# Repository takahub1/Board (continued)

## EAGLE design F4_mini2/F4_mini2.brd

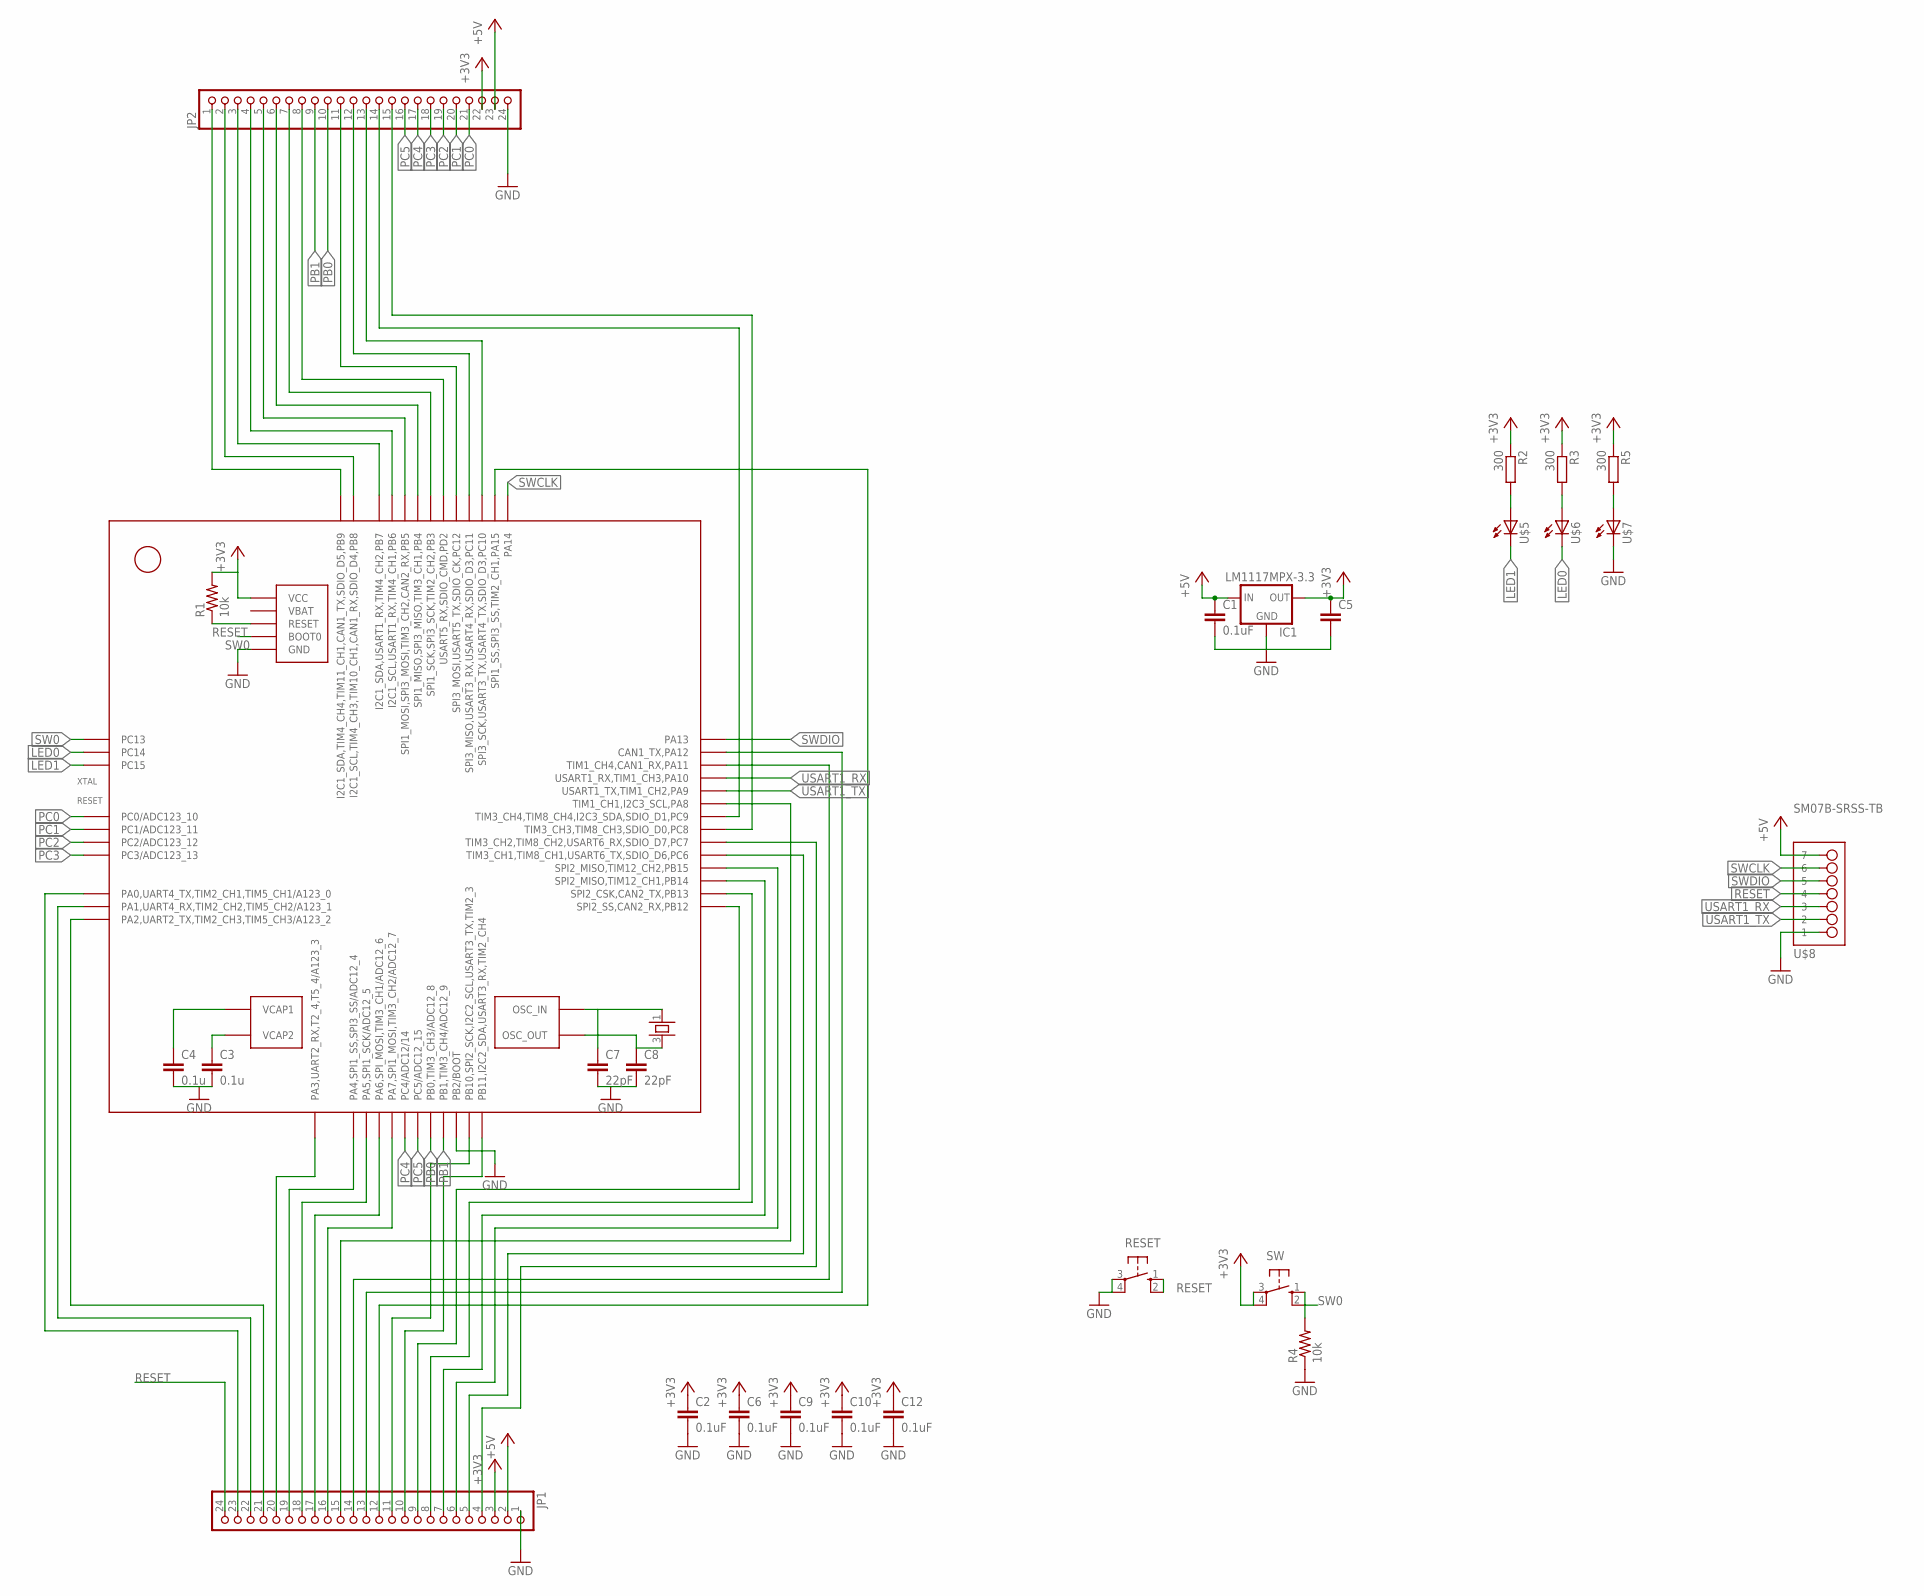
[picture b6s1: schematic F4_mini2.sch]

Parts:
C1: 0.1uF; C0603K
C2, C6, C9, C10, C12: 0.1uF; C0603
C3, C4: 0.1u; C0603K
C5: C-EUC0603K; C0603K
C7, C8: 22pF; C0603K
IC1: LM1117MPX-3.3; SOT223
JP1, JP2: PINHD-1X24; 1X24
R1, R4: 10k; R0603
R2, R3, R5: 300; R0603
RESET: 10-XX; B3F-10XX
SW: 10-XX; B3F-10XX
U$1: STM32F405_T; LQFP64
U$4: 25MHz; ASF
U$5, U$6, U$7: 0603
U$8: SM07B-SRSS-TB

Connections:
+3V3: C2.1, C5.1, C6.1, C9.1, C10.1, C12.1, IC1.2 (OUT1), IC1.4 (OUT), JP1.3, JP2.22, R1.2, R2.1, R3.1, R5.1, SW.3, SW.4 (P1), U$1.13 (VCC), U$1.19 (VCC), U$1.32 (VCC), U$1.48 (VCC), U$1.64 (VCC)
+5V: C1.1, IC1.3 (IN), JP1.2, JP2.23, U$8.P$7 (7)
A: JP2.3, U$1.59 (I2C1_SDA,USART1_RX,TIM4_CH2,PB7)
GND: C1.2, C2.2, C3.2, C4.2, C5.2, C6.2, C7.2, C8.2, C9.2, C10.2, C12.2, IC1.1 (GND), JP1.1, JP2.24, R4.1, RESET.3, RESET.4 (P1), U$1.12 (GND), U$1.18 (GND), U$1.28 (PB2/BOOT), U$1.63 (GND), U$7.C, U$8.P$1 (1)
LED0: U$1.3 (PC14), U$6.C
LED1: U$1.4 (PC15), U$5.C
unnamed: R2.2, U$5.A
unnamed: JP1.21, U$1.16 (PA2,UART2_TX,TIM2_CH3,TIM5_CH3/A123_2)
unnamed: JP1.23, U$1.14 (PA0,UART4_TX,TIM2_CH1,TIM5_CH1/A123_0)
unnamed: JP1.22, U$1.15 (PA1,UART4_RX,TIM2_CH2,TIM5_CH2/A123_1)
unnamed: JP1.15, U$1.41 (TIM1_CH1,I2C3_SCL,PA8)
unnamed: JP1.17, U$1.22 (PA6,SPI_MOSI,TIM3_CH1/ADC12_6)
unnamed: JP1.18, U$1.21 (PA5,SPI1_SCK/ADC12_5)
unnamed: JP1.19, U$1.20 (PA4,SPI1_SS,SPI3_SS/ADC12_4)
unnamed: JP1.20, U$1.17 (PA3,UART2_RX,T2_4,T5_4/A123_3)
unnamed: JP1.5, U$1.37 (TIM3_CH1,TIM8_CH1,USART6_TX,SDIO_D6,PC6)
unnamed: R3.2, U$6.A
unnamed: R5.2, U$7.A
unnamed: JP1.14, U$1.44 (TIM1_CH4,CAN1_RX,PA11)
unnamed: JP1.13, U$1.45 (CAN1_TX,PA12)
unnamed: JP1.4, U$1.38 (TIM3_CH2,TIM8_CH2,USART6_RX,SDIO_D7,PC7)
unnamed: JP1.16, U$1.23 (PA7,SPI1_MOSI,TIM3_CH2/ADC12_7)
unnamed: JP2.2, U$1.61 (I2C1_SCL,TIM4_CH3,TIM10_CH1,CAN1_RX,SDI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)
unnamed: JP2.1, U$1.62 (I2C1_SDA,TIM4_CH4,TIM11_CH1,CAN1_TX,SDI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)
unnamed: JP1.8, U$1.34 (SPI2_CSK,CAN2_TX,PB13)
unnamed: JP1.9, U$1.33 (SPI2_SS,CAN2_RX,PB12)
unnamed: JP1.10, U$1.30 (PB11,I2C2_SDA,USART3_RX,TIM2_CH4)
unnamed: JP1.11, U$1.29 (PB10,SPI2_SCK,I2C2_SCL,USART3_TX,TIM2_3)
unnamed: JP1.12, U$1.50 (SPI1_SS,SPI3_SS,TIM2_CH1,PA15)
unnamed: JP2.4, U$1.58 (I2C1_SCL,USART1_RX,TIM4_CH1,PB6)
unnamed: JP2.5, U$1.57 (SPI1_MOSI,SPI3_MOSI,TIM3_CH2,CAN2_RX,PB5)
unnamed: JP2.6, U$1.56 (SPI1_MISO,SPI3_MISO,TIM3_CH1,PB4)
unnamed: JP2.7, U$1.55 (SPI1_SCK,SPI3_SCK,TIM2_CH2,PB3)
unnamed: JP2.8, U$1.54 (USART5_RX,SDIO_CMD,PD2)
unnamed: JP2.11, U$1.53 (SPI3_MOSI,USART5_TX,SDIO_CK,PC12)
unnamed: JP2.12, U$1.52 (SPI3_MISO,USART3_RX,USART4_RX,SDIO_D3,P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)
unnamed: JP2.13, U$1.51 (SPI3_SCK,USART3_TX,USART4_TX,SDIO_D3,PC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)
unnamed: C3.1, U$1.47 (VCAP2)
unnamed: C4.1, U$1.31 (VCAP1)
unnamed: JP2.14, U$1.40 (TIM3_CH4,TIM8_CH4,I2C3_SDA,SDIO_D1,PC9)
unnamed: C7.1, U$1.5 (OSC_IN), U$4.1
unnamed: C8.1, U$1.6 (OSC_OUT), U$4.3
unnamed: JP2.15, U$1.39 (TIM3_CH3,TIM8_CH3,SDIO_D0,PC8)
PB0: JP2.10, U$1.26 (PB0,TIM3_CH3/ADC12_8)
PB1: JP2.9, U$1.27 (PB1,TIM3_CH4/ADC12_9)
PB14: JP1.7, U$1.35 (SPI2_MISO,TIM12_CH1,PB14)
PB15: JP1.6, U$1.36 (SPI2_MISO,TIM12_CH2,PB15)
PC0: JP2.21, U$1.8 (PC0/ADC123_10)
PC1: JP2.20, U$1.9 (PC1/ADC123_11)
PC2: JP2.19, U$1.10 (PC2/ADC123_12)
PC3: JP2.18, U$1.11 (PC3/ADC123_13)
PC4: JP2.17, U$1.24 (PC4/ADC12/14)
PC5: JP2.16, U$1.25 (PC5/ADC12_15)
RESET: JP1.24, R1.1, RESET.1 (S), RESET.2 (S1), U$1.7 (RESET), U$8.P$4 (4)
SW0: R4.2, SW.1 (S), SW.2 (S1), U$1.2 (PC13), U$1.60 (BOOT0)
SWCLK: U$1.49 (PA14), U$8.P$6 (6)
SWDIO: U$1.46 (PA13), U$8.P$5 (5)
USART1_RX: U$1.43 (USART1_RX,TIM1_CH3,PA10), U$8.P$3 (3)
USART1_TX: U$1.42 (USART1_TX,TIM1_CH2,PA9), U$8.P$2 (2)

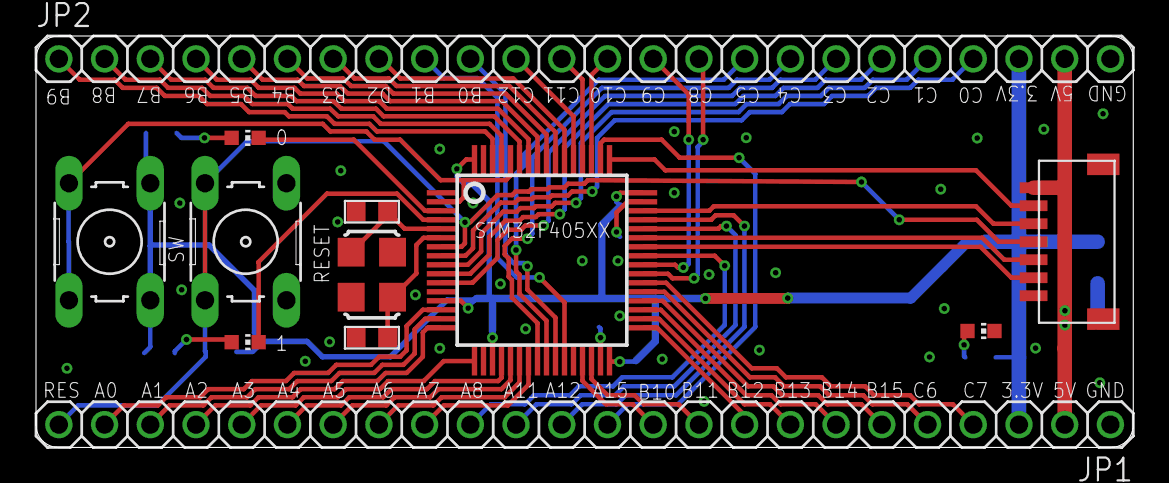
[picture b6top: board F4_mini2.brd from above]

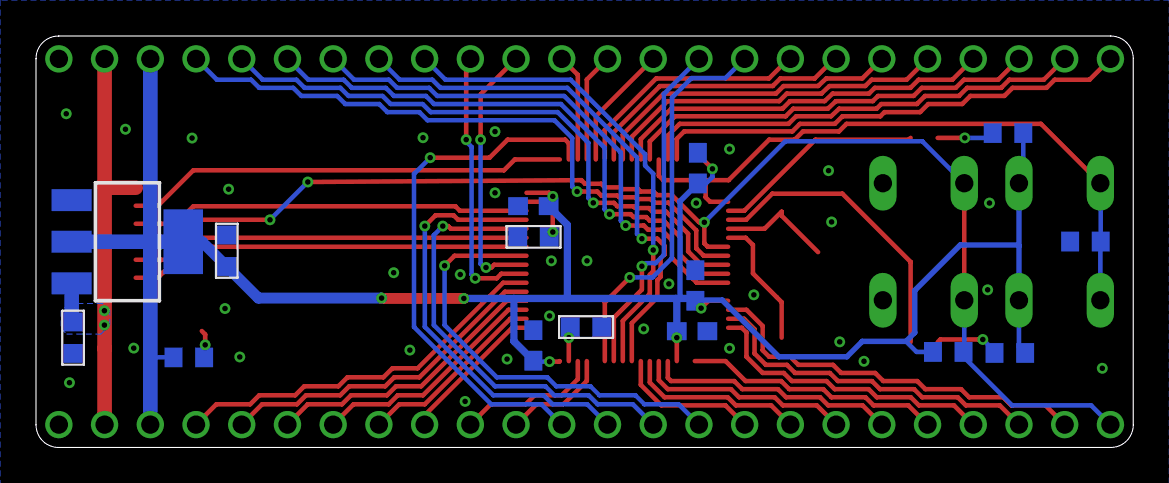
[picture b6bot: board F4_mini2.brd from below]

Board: 2 copper layers, 61.0 x 22.9 mm, 27 parts (15 on the bottom side), 59 nets.

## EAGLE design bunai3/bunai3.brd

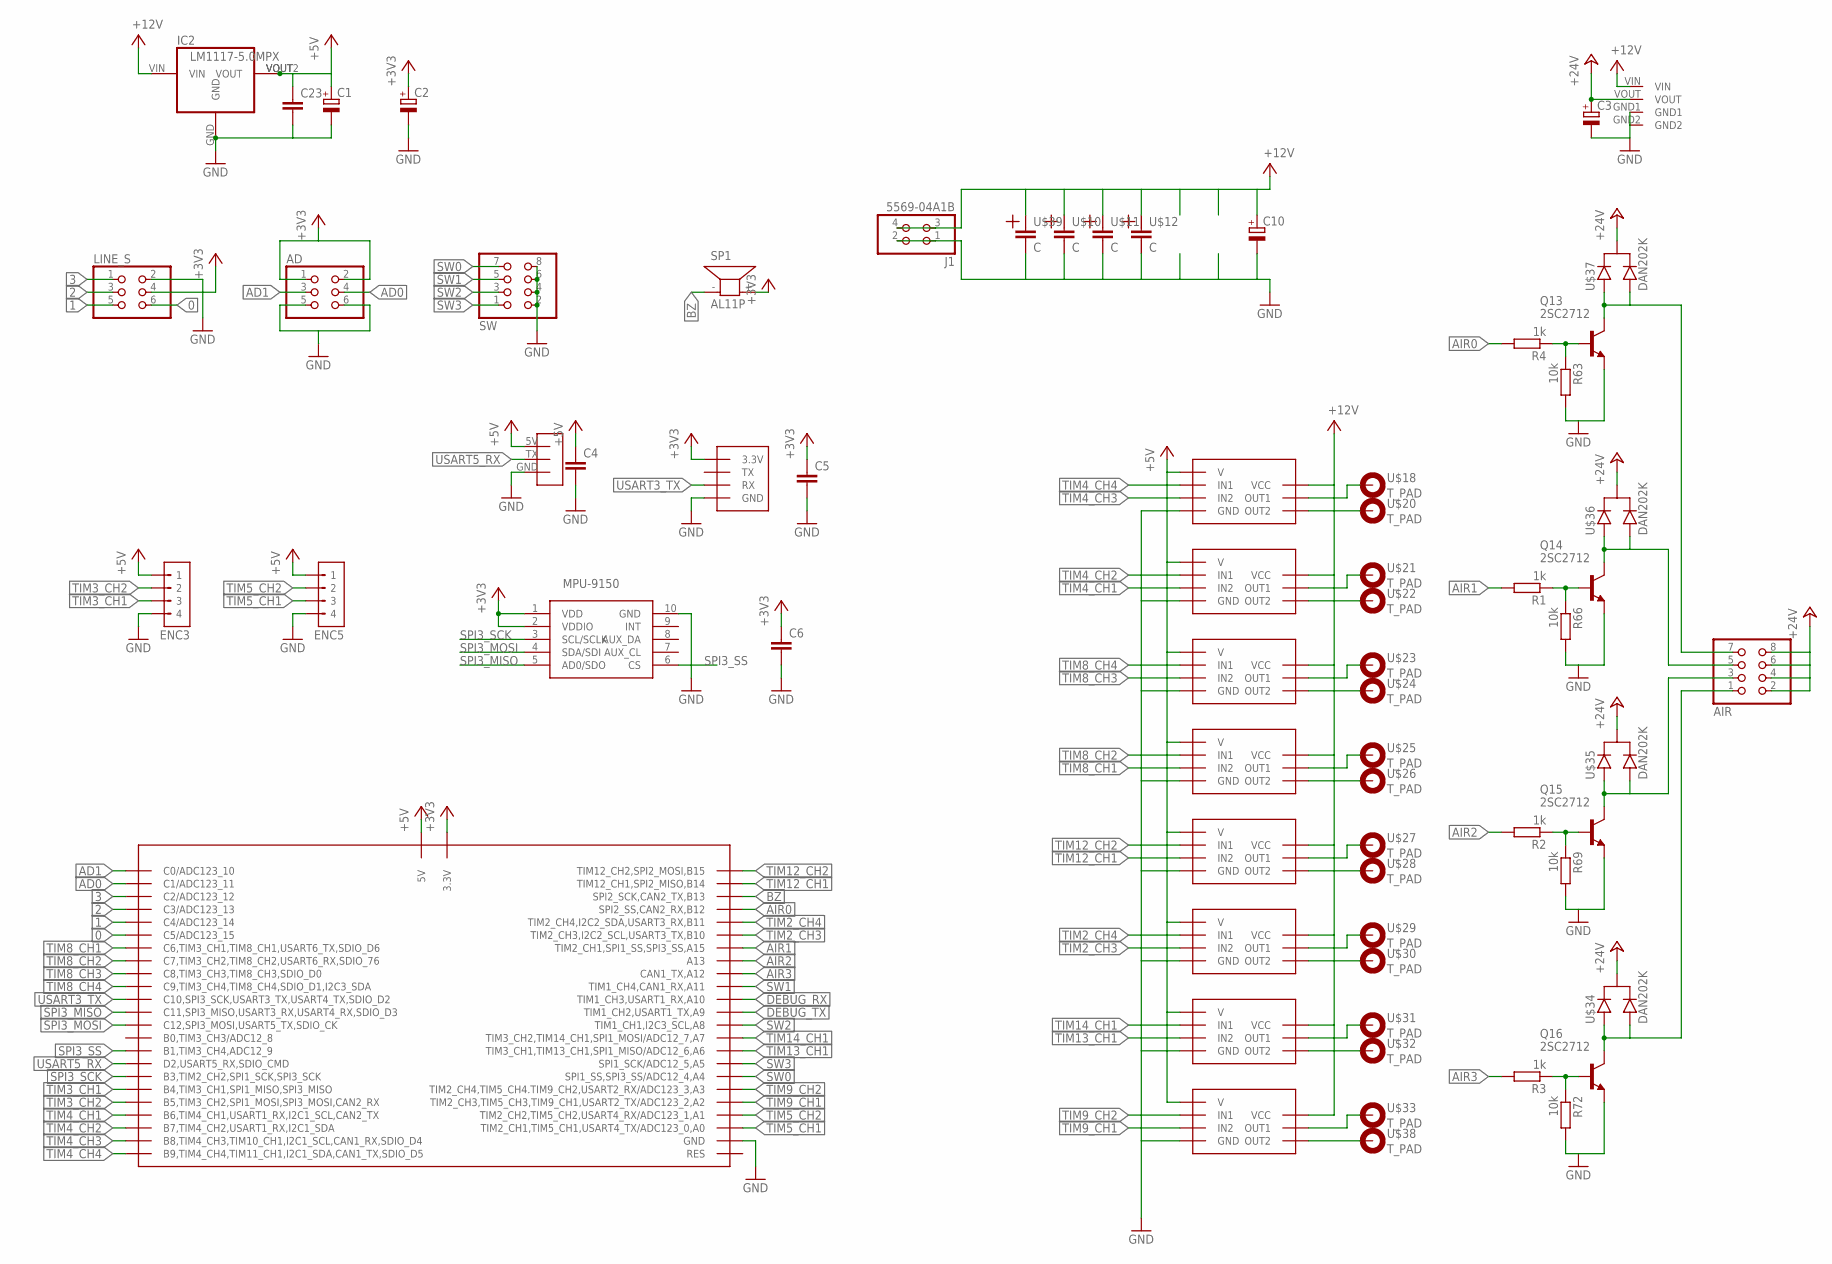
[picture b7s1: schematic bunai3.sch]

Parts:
AD: PINHD-2X3/90; 2X03/90
AIR: PINHD-2X4/90; 2X04/90
C1, C2, C3, C10: CPOL-EUE2.5-6; E2,5-6
C4, C5, C6: C-EU025-024X044; C025-024X044
C23: C-EUC0603K; C0603K
ENC3, ENC5: CN4-JST-XH-TOP; JST-B4B-XH-A
IC2: LM1117-5.0MPX; SOT223
J1: 5569-04A1B; 5569-04A1_2
LINE_S: PINHD-2X3/90; 2X03/90
MPU-9250: MPU-9250
Q13, Q14, Q15, Q16: 2SC2712; SC-59(TYPE1)
R1, R2, R3, R4: 1k; 0207/7
R63, R66, R69, R72: 10k; R0603
SP1: AL11P
SW: PINHD-2X4/90; 2X04/90
U$1: F4_T
U$2, U$3, U$4, U$5, U$6, U$7, U$8, U$9: BTM7752_T
U$10, U$11, U$12, U$39: C
U$16: LT3580
U$17: SBDBT_5V
U$18, U$20, U$21, U$22, U$23, U$24, U$25, U$26, U$27, U$28, U$29, U$30, U$31, U$32, U$33, U$38: T_PAD
U$19: XBEE_T
U$34, U$35, U$36, U$37: DAN202K; SC-59

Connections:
0: LINE_S.6, U$1.C5 (C5/ADC123_15)
1: LINE_S.5, U$1.C4 (C4/ADC123_14)
2: LINE_S.3, U$1.C3 (C3/ADC123_13)
3: LINE_S.1, U$1.C2 (C2/ADC123_12)
+3V3: AD.1, AD.2, C2.+, C5.1, C6.1, LINE_S.4, MPU-9250.1 (VDD), MPU-9250.2 (VDDIO), SP1.+ (2), U$1.3.3V, U$1.3.3V1 (3.3V), U$19.3.3V
+5V: C1.+, C4.1, C23.1, ENC3.1, ENC5.1, IC2.VOUT, IC2.VOUT2 (VOUT), U$1.5V, U$1.5V1 (5V), U$2.V, U$3.V, U$4.V, U$5.V, U$6.V, U$7.V, U$8.V, U$9.V, U$17.5V
+24V: AIR.2, AIR.4, AIR.6, AIR.8, C3.+, U$16.VOUT, U$34.K, U$35.K, U$36.K, U$37.K
AD0: AD.4, U$1.C1 (C1/ADC123_11)
AD1: AD.3, U$1.C0 (C0/ADC123_10)
AIR0: R4.2, U$1.B12 (SPI2_SS,CAN2_RX,B12)
AIR1: R1.2, U$1.A15 (TIM2_CH1,SPI1_SS,SPI3_SS,A15)
AIR2: R2.2, U$1.A13
AIR3: R3.2, U$1.A12 (CAN1_TX,A12)
BZ: SP1.- (1), U$1.B13 (SPI2_SCK,CAN2_TX,B13)
DEBUG_RX: U$1.A10 (TIM1_CH3,USART1_RX,A10)
DEBUG_TX: U$1.A9 (TIM1_CH2,USART1_TX,A9)
GND: AD.5, AD.6, C1.-, C2.-, C3.-, C4.2, C5.2, C6.2, C10.-, C23.2, ENC3.4, ENC5.4, IC2.GND, J1.1, J1.2, LINE_S.2, MPU-9250.10 (GND), Q13.E, Q14.E, Q15.E, Q16.E, R63.2, R66.2, R69.2, R72.2, SW.2, SW.4, SW.6, SW.8, U$1.GND1 (GND), U$1.GND2 (GND), U$1.GND3 (GND), U$2.GND1 (GND), U$2.GND2 (GND), U$2.GND3 (GND), U$3.GND1 (GND), U$3.GND2 (GND), U$3.GND3 (GND), U$4.GND1 (GND), U$4.GND2 (GND), U$4.GND3 (GND), U$5.GND1 (GND), U$5.GND2 (GND), U$5.GND3 (GND), U$6.GND1 (GND), U$6.GND2 (GND), U$6.GND3 (GND), U$7.GND1 (GND), U$7.GND2 (GND), U$7.GND3 (GND), U$8.GND1 (GND), U$8.GND2 (GND), U$8.GND3 (GND), U$9.GND1 (GND), U$9.GND2 (GND), U$9.GND3 (GND), U$16.GND1, U$16.GND2, U$17.GND, U$19.GND
unnamed: U$9.OUT11 (OUT1), U$9.OUT12 (OUT1), U$9.OUT13 (OUT1), U$9.OUT14 (OUT1), U$18.P$1
unnamed: U$9.OUT21 (OUT2), U$9.OUT22 (OUT2), U$9.OUT23 (OUT2), U$9.OUT24 (OUT2), U$20.P$1
unnamed: U$8.OUT11 (OUT1), U$8.OUT12 (OUT1), U$8.OUT13 (OUT1), U$8.OUT14 (OUT1), U$21.P$1
unnamed: U$8.OUT21 (OUT2), U$8.OUT22 (OUT2), U$8.OUT23 (OUT2), U$8.OUT24 (OUT2), U$22.P$1
unnamed: U$7.OUT11 (OUT1), U$7.OUT12 (OUT1), U$7.OUT13 (OUT1), U$7.OUT14 (OUT1), U$23.P$1
unnamed: U$7.OUT21 (OUT2), U$7.OUT22 (OUT2), U$7.OUT23 (OUT2), U$7.OUT24 (OUT2), U$24.P$1
unnamed: U$6.OUT11 (OUT1), U$6.OUT12 (OUT1), U$6.OUT13 (OUT1), U$6.OUT14 (OUT1), U$25.P$1
unnamed: U$6.OUT21 (OUT2), U$6.OUT22 (OUT2), U$6.OUT23 (OUT2), U$6.OUT24 (OUT2), U$26.P$1
unnamed: U$5.OUT11 (OUT1), U$5.OUT12 (OUT1), U$5.OUT13 (OUT1), U$5.OUT14 (OUT1), U$27.P$1
unnamed: U$5.OUT21 (OUT2), U$5.OUT22 (OUT2), U$5.OUT23 (OUT2), U$5.OUT24 (OUT2), U$28.P$1
unnamed: U$4.OUT11 (OUT1), U$4.OUT12 (OUT1), U$4.OUT13 (OUT1), U$4.OUT14 (OUT1), U$29.P$1
unnamed: U$4.OUT21 (OUT2), U$4.OUT22 (OUT2), U$4.OUT23 (OUT2), U$4.OUT24 (OUT2), U$30.P$1
unnamed: U$3.OUT11 (OUT1), U$3.OUT12 (OUT1), U$3.OUT13 (OUT1), U$3.OUT14 (OUT1), U$31.P$1
unnamed: U$3.OUT21 (OUT2), U$3.OUT22 (OUT2), U$3.OUT23 (OUT2), U$3.OUT24 (OUT2), U$32.P$1
unnamed: U$2.OUT11 (OUT1), U$2.OUT12 (OUT1), U$2.OUT13 (OUT1), U$2.OUT14 (OUT1), U$33.P$1
unnamed: U$2.OUT21 (OUT2), U$2.OUT22 (OUT2), U$2.OUT23 (OUT2), U$2.OUT24 (OUT2), U$38.P$1
unnamed: Q13.B, R4.1, R63.1
unnamed: AIR.7, Q13.C, U$37.A@1 (A1), U$37.A@2 (A2)
unnamed: Q14.B, R1.1, R66.1
unnamed: AIR.5, Q14.C, U$36.A@1 (A1), U$36.A@2 (A2)
unnamed: Q15.B, R2.1, R69.1
unnamed: AIR.3, Q15.C, U$35.A@1 (A1), U$35.A@2 (A2)
unnamed: AIR.1, Q16.C, U$34.A@1 (A1), U$34.A@2 (A2)
unnamed: Q16.B, R3.1, R72.1
SPI3_MISO: MPU-9250.5 (AD0/SDO), U$1.C11 (C11,SPI3_MISO,USART3_RX,USART4_RX,SDIO_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)
SPI3_MOSI: MPU-9250.4 (SDA/SDI), U$1.C12 (C12,SPI3_MOSI,USART5_TX,SDIO_CK)
SPI3_SCK: MPU-9250.3 (SCL/SCLK), U$1.B3 (B3,TIM2_CH2,SPI1_SCK,SPI3_SCK)
SPI3_SS: MPU-9250.6 (CS), U$1.B1 (B1,TIM3_CH4,ADC12_9)
SW0: SW.7, U$1.A4 (SPI1_SS,SPI3_SS/ADC12_4,A4)
SW1: SW.5, U$1.A11 (TIM1_CH4,CAN1_RX,A11)
SW2: SW.3, U$1.A8 (TIM1_CH1,I2C3_SCL,A8)
SW3: SW.1, U$1.A5 (SPI1_SCK/ADC12_5,A5)
TIM2_CH3: U$1.B10 (TIM2_CH3,I2C2_SCL,USART3_TX,B10), U$4.IN2
TIM2_CH4: U$1.B11 (TIM2_CH4,I2C2_SDA,USART3_RX,B11), U$4.IN1
TIM3_CH1: ENC3.3, U$1.B4 (B4,TIM3_CH1,SPI1_MISO,SPI3_MISO)
TIM3_CH2: ENC3.2, U$1.B5 (B5,TIM3_CH2,SPI1_MOSI,SPI3_MOSI,CAN2_RX)
TIM4_CH1: U$1.B6 (B6,TIM4_CH1,USART1_RX,I2C1_SCL,CAN2_TX), U$8.IN2
TIM4_CH2: U$1.B7 (B7,TIM4_CH2,USART1_RX,I2C1_SDA), U$8.IN1
TIM4_CH3: U$1.B8 (B8,TIM4_CH3,TIM10_CH1,I2C1_SCL,CAN1_RX,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), U$9.IN2
TIM4_CH4: U$1.B9 (B9,TIM4_CH4,TIM11_CH1,I2C1_SDA,CAN1_TX,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), U$9.IN1
TIM5_CH1: ENC5.3, U$1.A0 (TIM2_CH1,TIM5_CH1,USART4_TX/ADC123_0,A0)
TIM5_CH2: ENC5.2, U$1.A1 (TIM2_CH2,TIM5_CH2,USART4_RX/ADC123_1,A1)
TIM8_CH1: U$1.C6 (C6,TIM3_CH1,TIM8_CH1,USART6_TX,SDIO_D6), U$6.IN2
TIM8_CH2: U$1.C7 (C7,TIM3_CH2,TIM8_CH2,USART6_RX,SDIO_76), U$6.IN1
TIM8_CH3: U$1.C8 (C8,TIM3_CH3,TIM8_CH3,SDIO_D0), U$7.IN2
TIM8_CH4: U$1.C9 (C9,TIM3_CH4,TIM8_CH4,SDIO_D1,I2C3_SDA), U$7.IN1
TIM9_CH1: U$1.A2 (TIM2_CH3,TIM5_CH3,TIM9_CH1,USART2_TX/AD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), U$2.IN2
TIM9_CH2: U$1.A3 (TIM2_CH4,TIM5_CH4.TIM9_CH2,USART2_RX/AD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), U$2.IN1
TIM12_CH1: U$1.B14 (TIM12_CH1,SPI2_MISO,B14), U$5.IN2
TIM12_CH2: U$1.B15 (TIM12_CH2,SPI2_MOSI,B15), U$5.IN1
TIM13_CH1: U$1.A6 (TIM3_CH1,TIM13_CH1,SPI1_MISO/ADC12_6,A6), U$3.IN2
TIM14_CH1: U$1.A7 (TIM3_CH2,TIM14_CH1,SPI1_MOSI/ADC12_7,A7), U$3.IN1
USART3_TX: U$1.C10 (C10,SPI3_SCK,USART3_TX,USART4_TX,SDIO_D2), U$19.RX
USART5_RX: U$1.D2 (D2,USART5_RX,SDIO_CMD), U$17.TX (TX_5V)
V+: C10.+, IC2.VIN, J1.3, J1.4, U$2.VCC1 (VCC), U$2.VCC2 (VCC), U$2.VCC3 (VCC), U$2.VCC4 (VCC), U$3.VCC1 (VCC), U$3.VCC2 (VCC), U$3.VCC3 (VCC), U$3.VCC4 (VCC), U$4.VCC1 (VCC), U$4.VCC2 (VCC), U$4.VCC3 (VCC), U$4.VCC4 (VCC), U$5.VCC1 (VCC), U$5.VCC2 (VCC), U$5.VCC3 (VCC), U$5.VCC4 (VCC), U$6.VCC1 (VCC), U$6.VCC2 (VCC), U$6.VCC3 (VCC), U$6.VCC4 (VCC), U$7.VCC1 (VCC), U$7.VCC2 (VCC), U$7.VCC3 (VCC), U$7.VCC4 (VCC), U$8.VCC1 (VCC), U$8.VCC2 (VCC), U$8.VCC3 (VCC), U$8.VCC4 (VCC), U$9.VCC1 (VCC), U$9.VCC2 (VCC), U$9.VCC3 (VCC), U$9.VCC4 (VCC), U$16.VIN

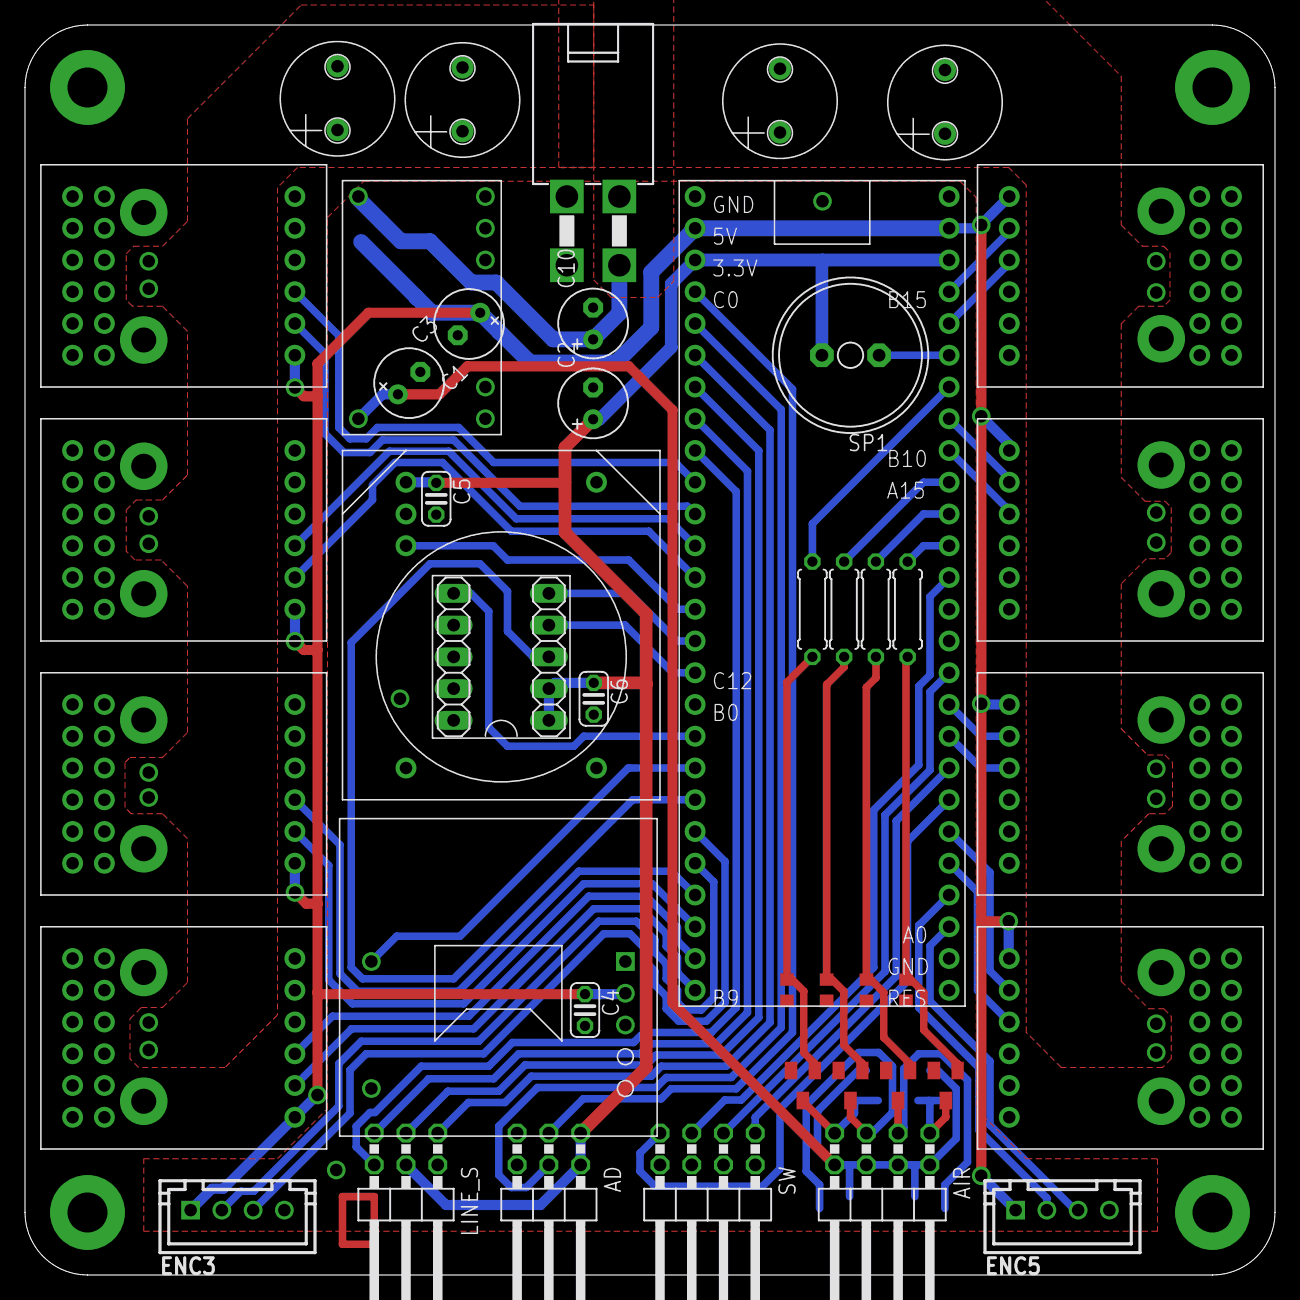
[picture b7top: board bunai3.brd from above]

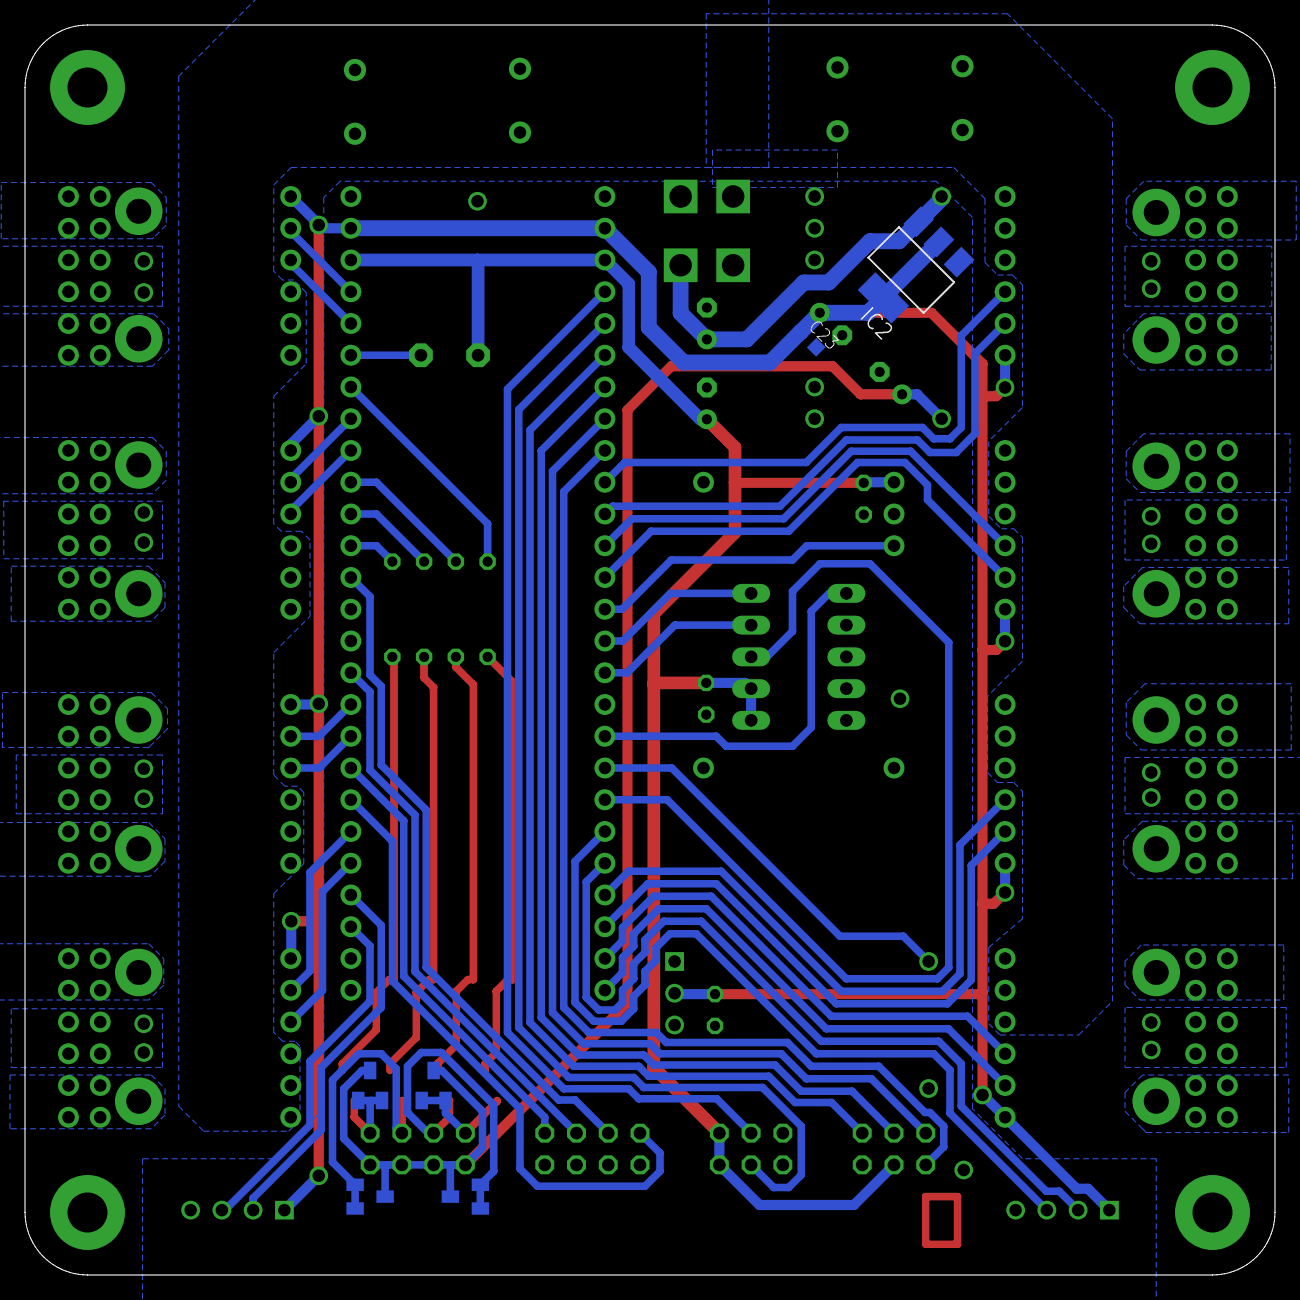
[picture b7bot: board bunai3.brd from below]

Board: 2 copper layers, 100.0 x 100.0 mm, 66 parts (6 on the bottom side), 70 nets.

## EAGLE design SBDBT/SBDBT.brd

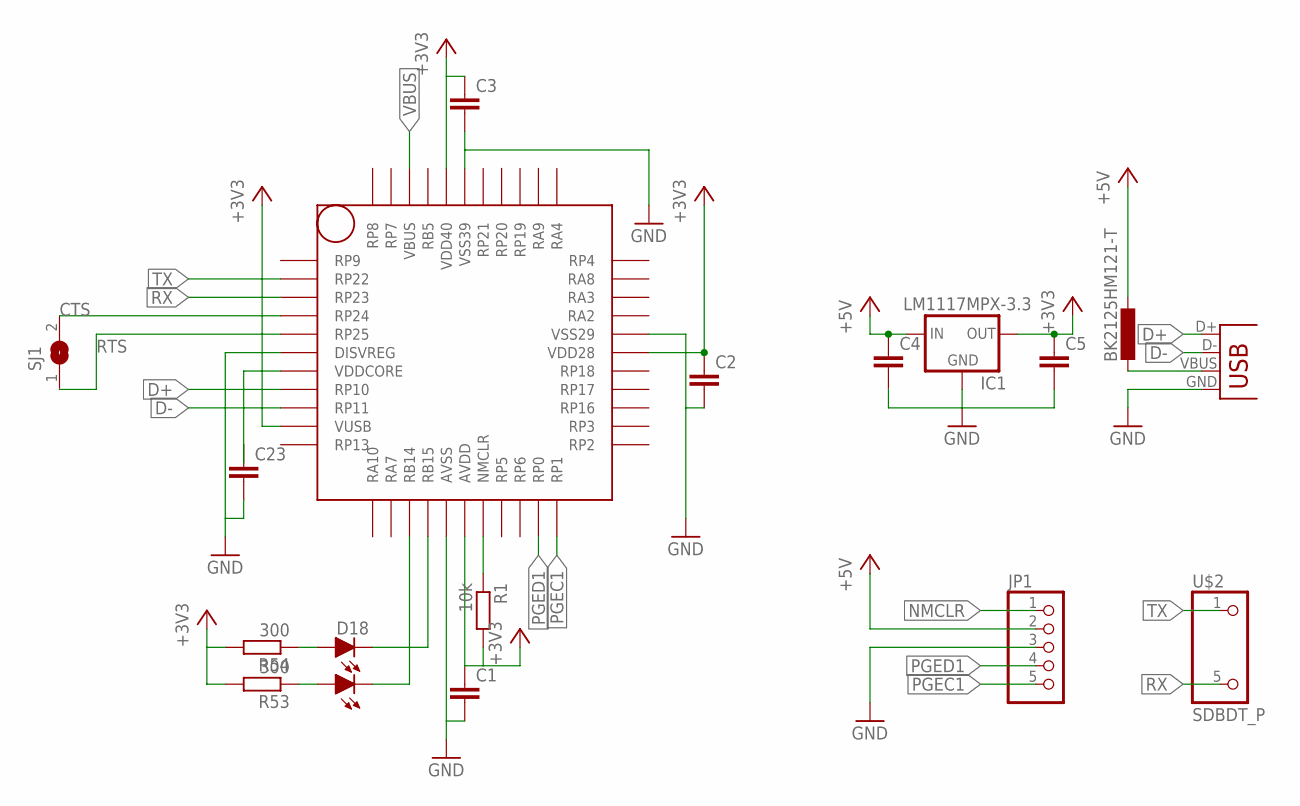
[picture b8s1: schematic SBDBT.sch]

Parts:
BK2125HM121-T: L-EUL2012C; L2012C
C1, C2, C3, C4, C5, C23: C-EUC0603K; C0603K
D18: SEC2XX4; LED3025
IC1: LM1117MPX-3.3; SOT223
JP1: PINHD-1X5; 1X05
R1: 10k; R0603
R53, R54: 300; R0603
SJ1: SJ
U$1: PIC24FJ64GB004; SQFP-S-10X10-44
U$2: SDBDT_P
X2: USB_; USB-A-S-SILK-FEMALE

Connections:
+3V3: C1.1, C2.1, C3.1, C5.1, IC1.2 (OUT1), IC1.4 (OUT), R1.2, R53.2, R54.2, U$1.AVDD, U$1.VDD28, U$1.VDD40, U$1.VUSB
+5V: BK2125HM121-T.1, C4.1, IC1.3 (IN), JP1.2
CTS: SJ1.2, U$1.RP24
D+: U$1.RP10, X2.D+
D-: U$1.RP11, X2.D-
GND: C1.2, C2.2, C3.2, C4.2, C5.2, C23.2, IC1.1 (GND), JP1.3, U$1.AVSS, U$1.DISVREG, U$1.VSS29, U$1.VSS39, X2.GND
unnamed: D18.2 (C1), U$1.RB14
unnamed: D18.1 (C0), U$1.RB15
unnamed: C23.1, U$1.VDDCORE
unnamed: D18.3 (A1), R53.1
unnamed: D18.4 (A0), R54.1
NMCLR: JP1.1, R1.1, U$1.NMCLR
PGEC1: JP1.5, U$1.RP1
PGED1: JP1.4, U$1.RP0
RTS: SJ1.1, U$1.RP25
RX: U$1.RP23, U$2.5
TX: U$1.RP22, U$2.1
VBUS: BK2125HM121-T.2, U$1.VBUS, X2.VBUS

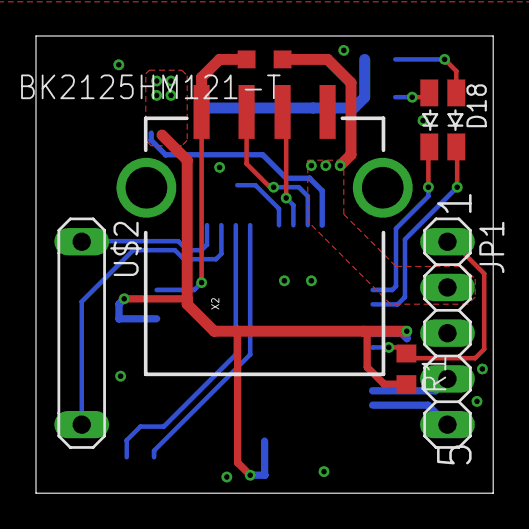
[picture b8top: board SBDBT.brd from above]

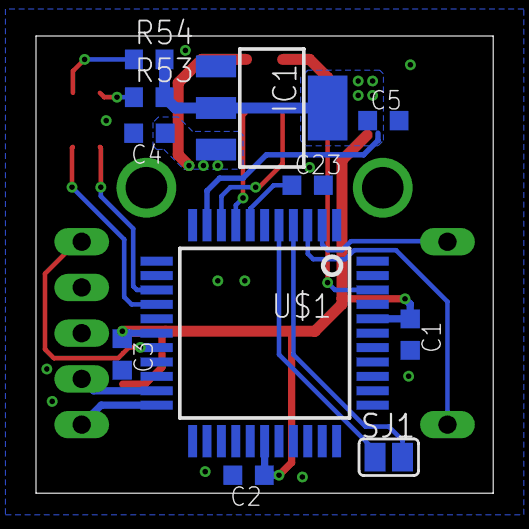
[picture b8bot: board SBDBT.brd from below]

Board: 2 copper layers, 25.4 x 25.4 mm, 17 parts (11 on the bottom side), 18 nets.

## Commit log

2016-12-13 first
2017-04-27 add fallBz 2,3
